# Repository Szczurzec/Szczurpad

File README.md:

# Szczurpad

The Szczurpad is my first real electronics project, it features 9 keys, an ec11 rotary encoder and an OLED display and uses QMK firmware 🤯

# CAD
the case has 2 parts

# PCB

The PCB:

The Schematic:

## Firmware features
made using [QMK](https://qmk.fm/)
- the rotary encoder has different functions depending on the layer, it can either change volume or scroll websites.
- The OLED shows the current layer, numlock, capslock and scroll lock status

## BOM:
Here are all the parts needed for assembly:

- 9x Cherry MX Switches
- 9x DSA Keycaps
- 4x M3x16mm screws
- 4x M3x5mx4mm heatset inserts
- 9x 1N4148 DO-35 Diodes.
- 1x 0.91" 128x32 OLED Display
- 1x EC11 Rotary Encoder
- 1x XIAO RP2040
- 1x Case (2 printed parts)

#### (will improve this further in the future)

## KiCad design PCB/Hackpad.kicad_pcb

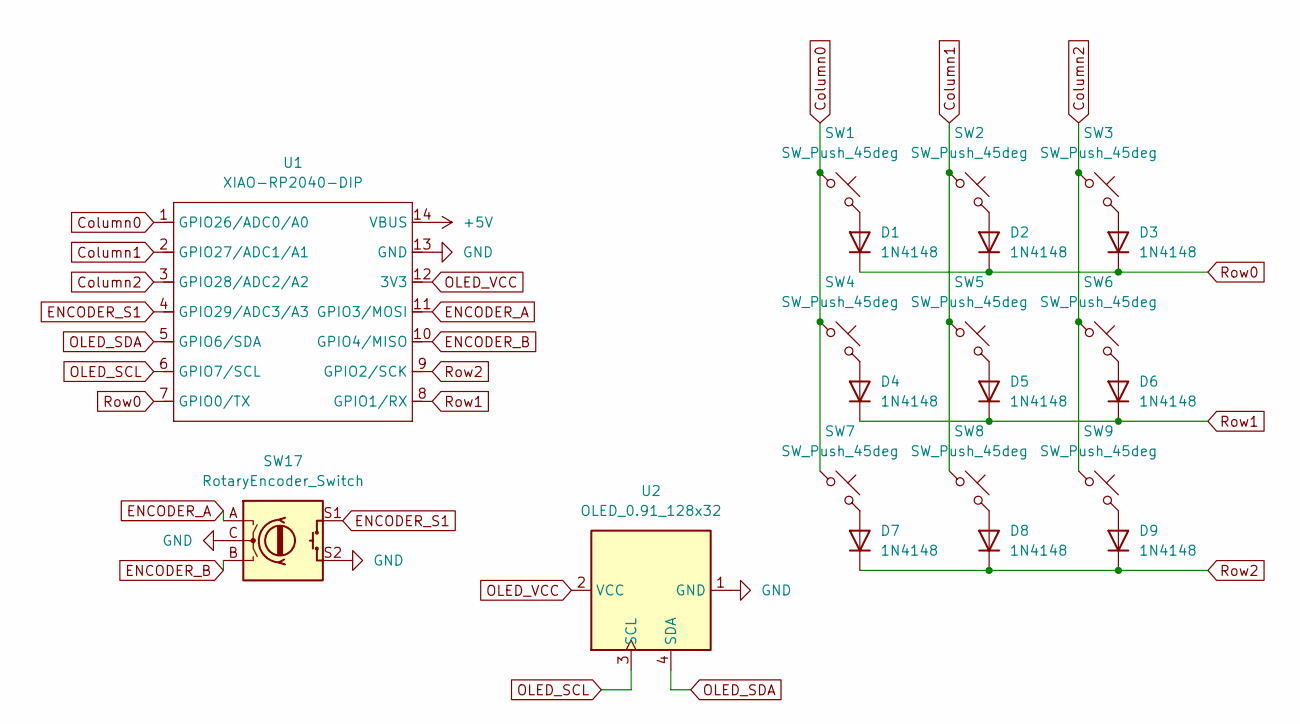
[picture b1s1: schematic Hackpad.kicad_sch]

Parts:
D1, D2, D3, D4, D5, D6, D7, D8, D9: 1N4148; D_DO-35_SOD27_P7.62mm_Horizontal
SW1, SW2, SW3, SW4, SW5, SW6, SW7, SW8, SW9: SW_Push_45deg; SW_Cherry_MX_1.00u_PCB
SW17: RotaryEncoder_Switch; RotaryEncoder_Alps_EC11E-Switch_Vertical_H20mm
U1: XIAO-RP2040-DIP
U2: OLED_0.91_128x32

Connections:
+5V: U1.14 (VBUS)
Column0: SW1.1, SW4.1, SW7.1, U1.1 (GPIO26/ADC0/A0)
Column1: SW2.1, SW5.1, SW8.1, U1.2 (GPIO27/ADC1/A1)
Column2: SW3.1, SW6.1, SW9.1, U1.3 (GPIO28/ADC2/A2)
ENCODER_A: SW17.A, U1.11 (GPIO3/MOSI)
ENCODER_B: SW17.B, U1.10 (GPIO4/MISO)
ENCODER_S1: SW17.S1, U1.4 (GPIO29/ADC3/A3)
GND: SW17.C, SW17.S2, U1.13 (GND), U2.1 (GND)
unnamed: D1.2 (A), SW1.2
unnamed: D2.2 (A), SW2.2
unnamed: D3.2 (A), SW3.2
unnamed: D4.2 (A), SW4.2
unnamed: D5.2 (A), SW5.2
unnamed: D6.2 (A), SW6.2
unnamed: D7.2 (A), SW7.2
unnamed: D8.2 (A), SW8.2
unnamed: D9.2 (A), SW9.2
OLED_SCL: U1.6 (GPIO7/SCL), U2.3 (SCL)
OLED_SDA: U1.5 (GPIO6/SDA), U2.4 (SDA)
OLED_VCC: U1.12 (3V3), U2.2 (VCC)
Row0: D1.1 (K), D2.1 (K), D3.1 (K), U1.7 (GPIO0/TX)
Row1: D4.1 (K), D5.1 (K), D6.1 (K), U1.8 (GPIO1/RX)
Row2: D7.1 (K), D8.1 (K), D9.1 (K), U1.9 (GPIO2/SCK)

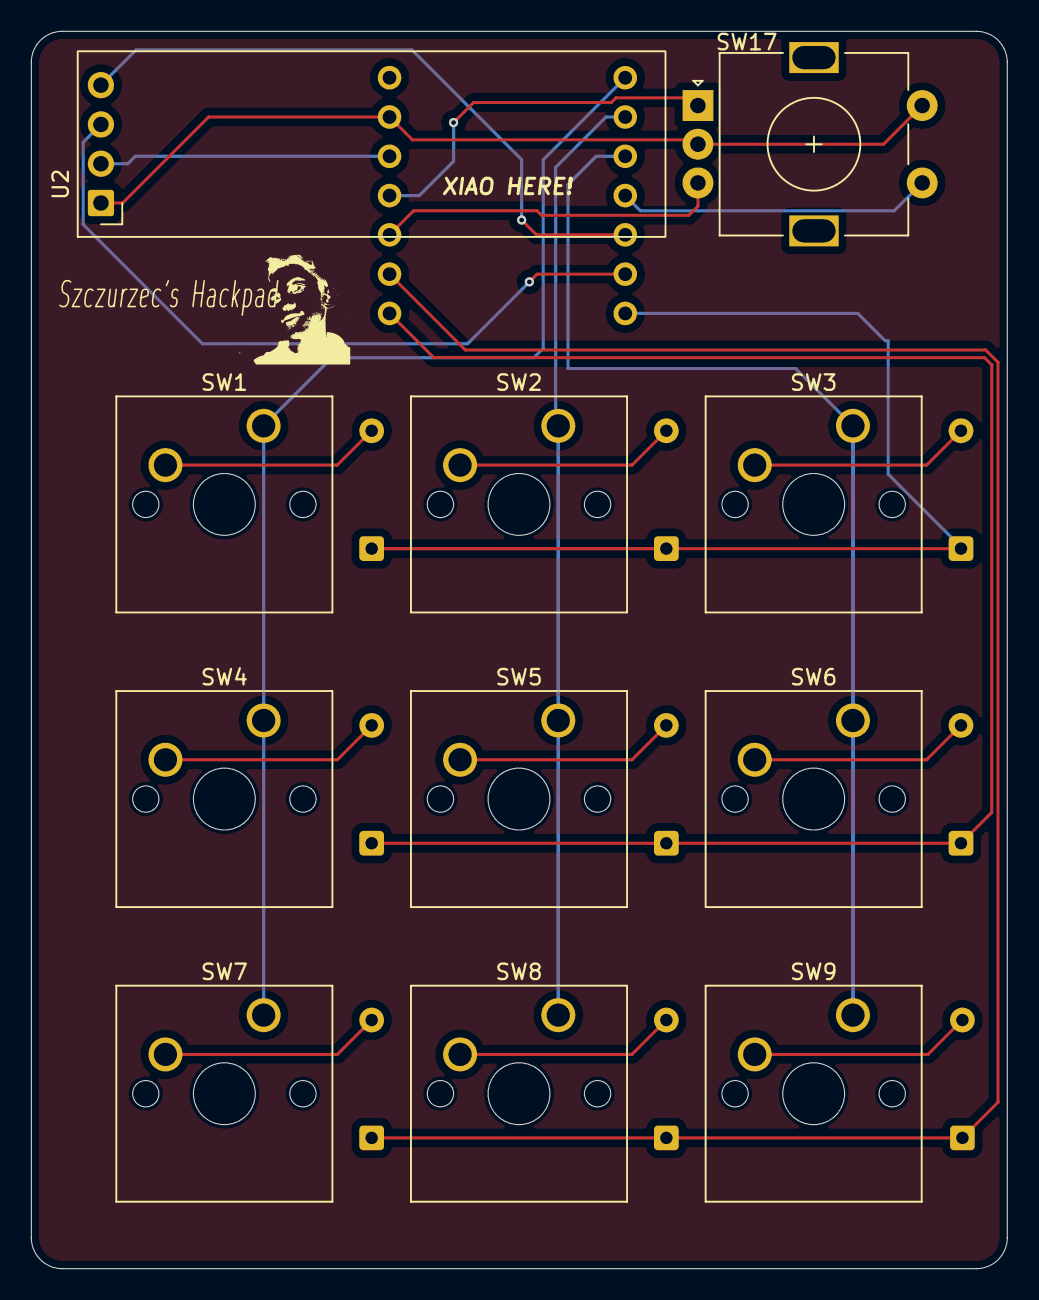
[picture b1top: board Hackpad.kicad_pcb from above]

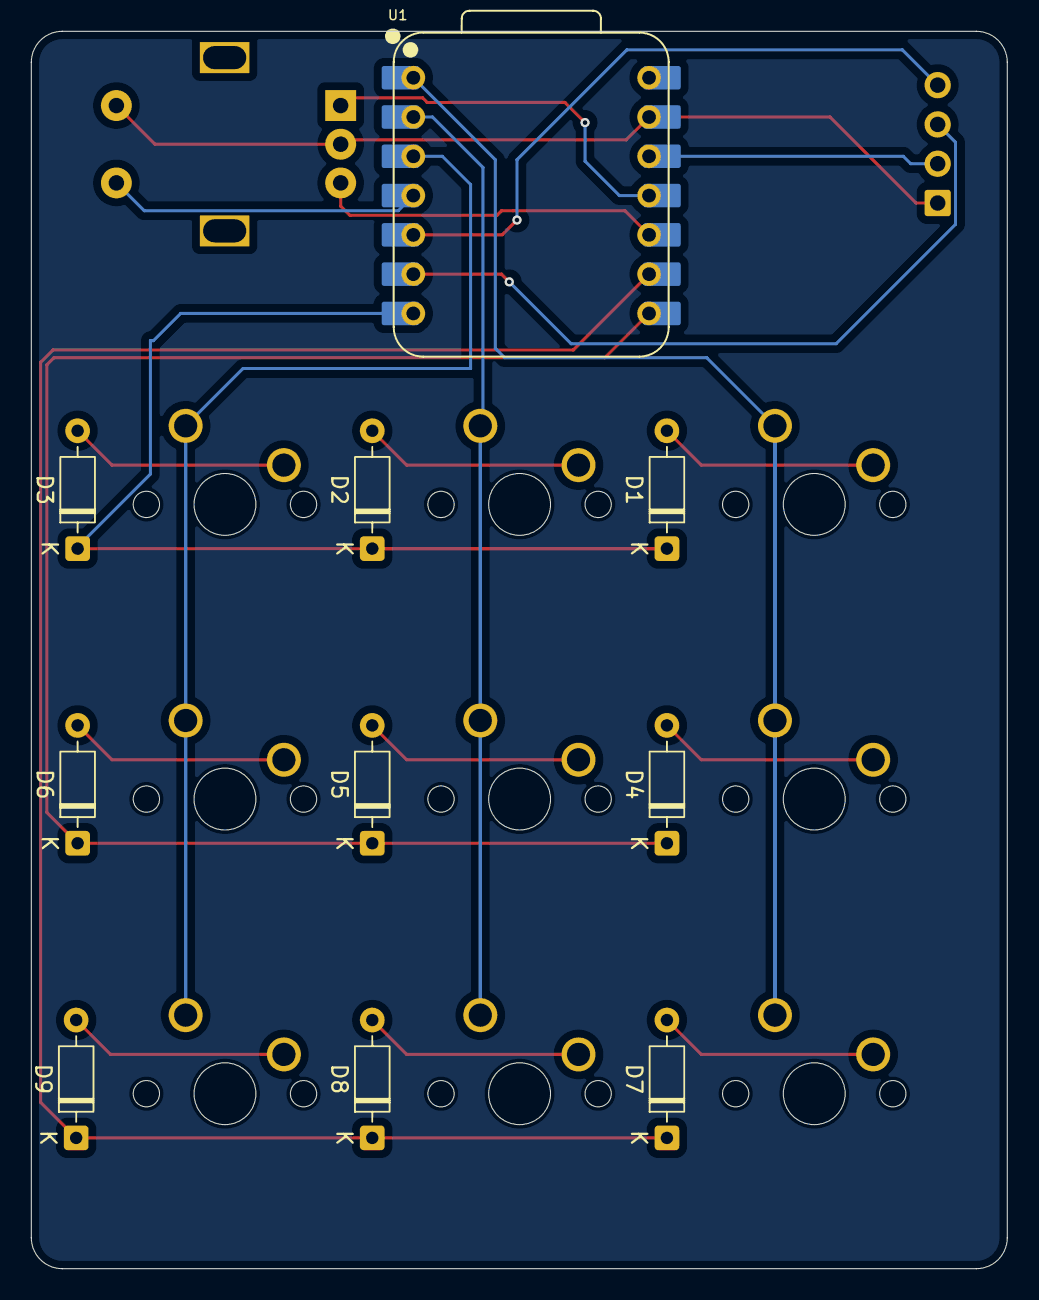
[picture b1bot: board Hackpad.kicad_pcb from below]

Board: 2 copper layers, 63.1 x 80.0 mm, 21 parts (10 on the bottom side), 22 nets.

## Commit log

2026-01-29 Upload firmware
2026-01-30 case upload
2026-01-30 Upload case
2026-01-30 Upload pcb
2026-02-06 production
2026-03-29 test
2026-03-29 Add new image to README
    Added an additional image to the README.
2026-03-29 real reasdme
